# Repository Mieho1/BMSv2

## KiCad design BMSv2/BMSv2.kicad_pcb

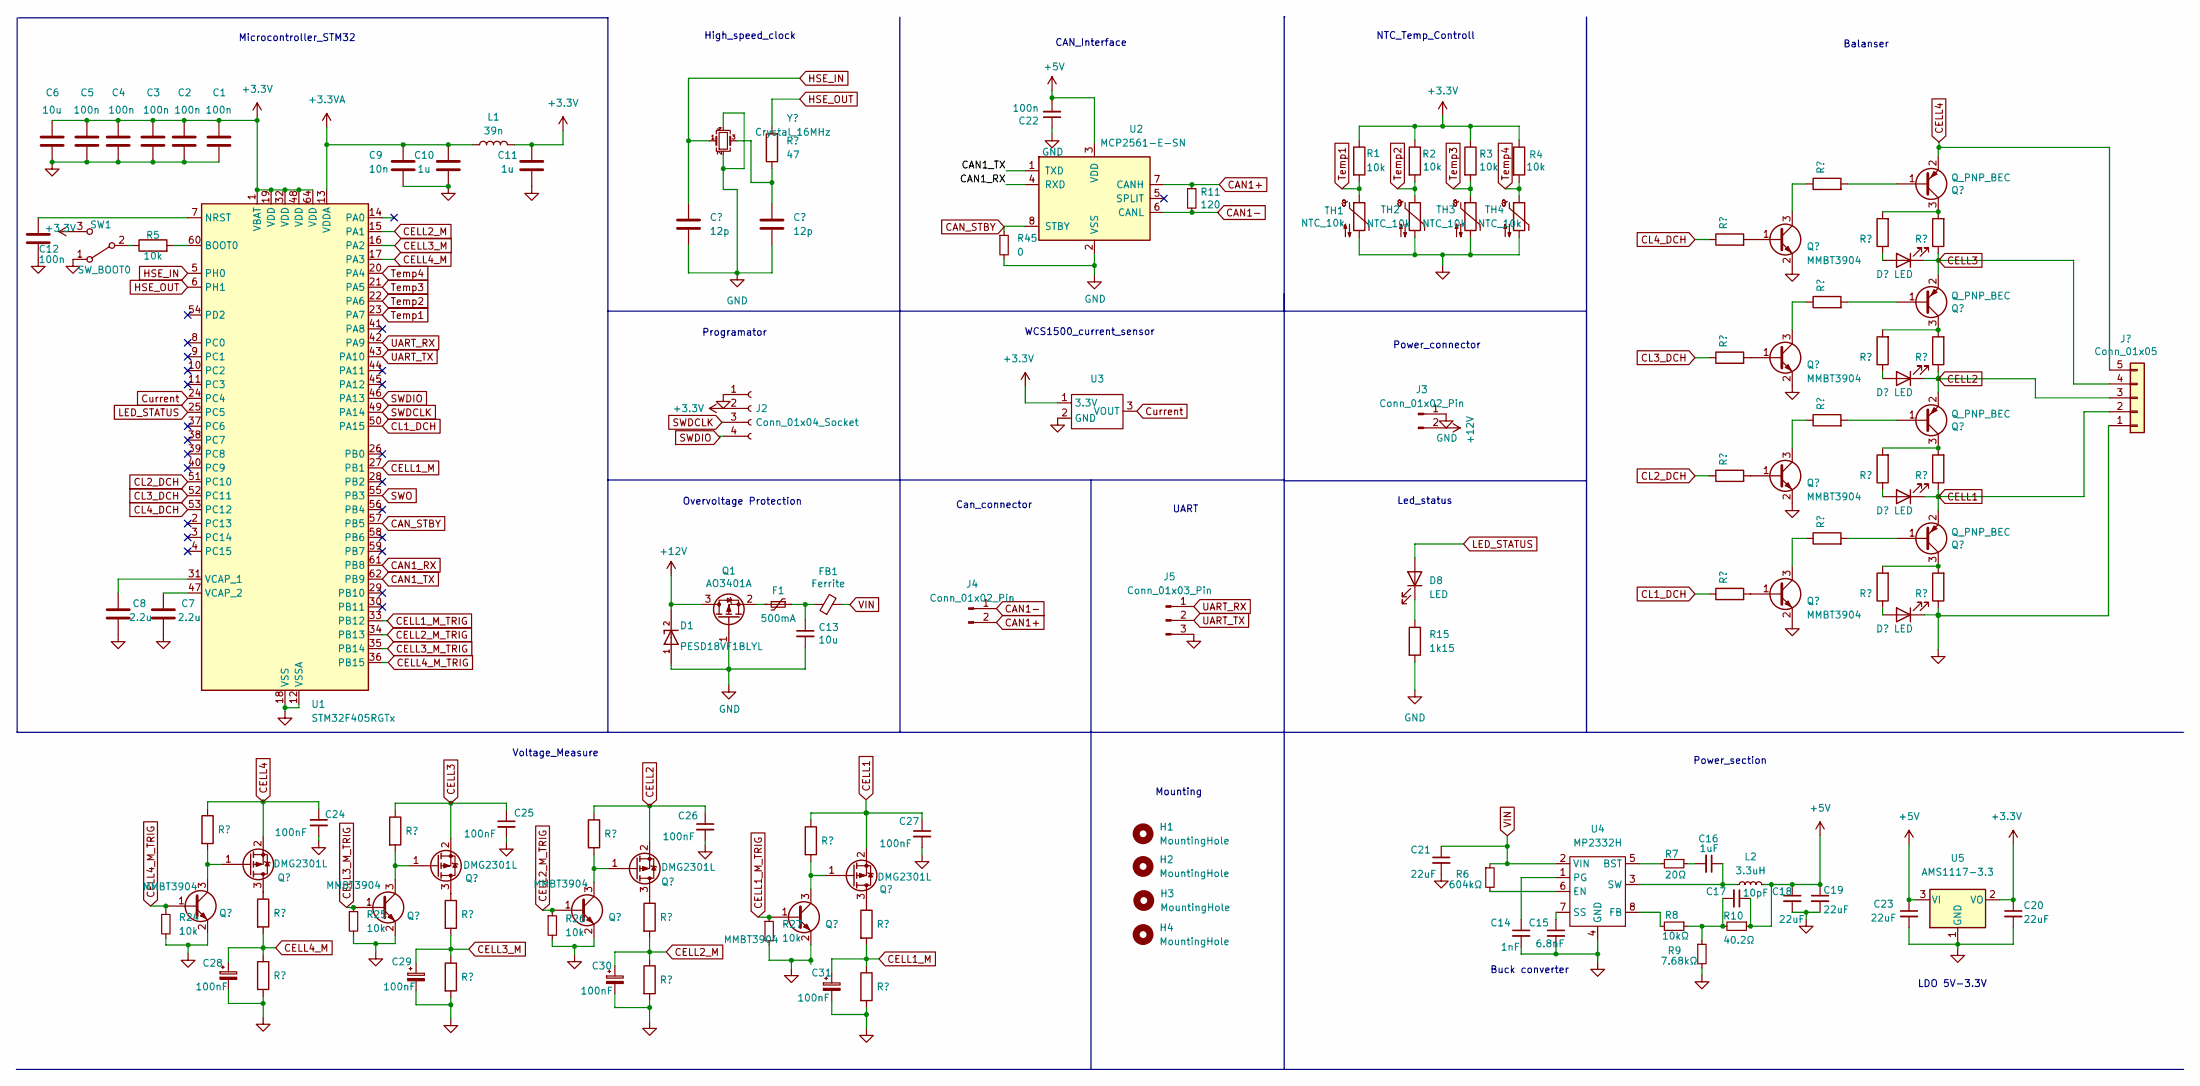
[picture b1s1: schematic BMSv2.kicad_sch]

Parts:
C1, C2, C3, C4, C5, C12, C22: 100n; C_0402_1005Metric_Pad0.74x0.62mm_HandSolder
C6, C13: 10u; C_0402_1005Metric_Pad0.74x0.62mm_HandSolder
C7, C8: 2.2u; C_0402_1005Metric_Pad0.74x0.62mm_HandSolder
C9: 10n; C_0402_1005Metric_Pad0.74x0.62mm_HandSolder
C10, C11: 1u; C_0402_1005Metric_Pad0.74x0.62mm_HandSolder
C14: 1nF; C_0402_1005Metric_Pad0.74x0.62mm_HandSolder
C15: 6.8nF; C_0402_1005Metric_Pad0.74x0.62mm_HandSolder
C16: 1uF; C_0402_1005Metric_Pad0.74x0.62mm_HandSolder
C17: 10pF; C_0402_1005Metric_Pad0.74x0.62mm_HandSolder
C18, C19, C20, C21, C23: 22uF; C_0805_2012Metric_Pad1.18x1.45mm_HandSolder
C24, C25, C26, C27, C28, C29, C30, C31: 100nF; C_0402_1005Metric_Pad0.74x0.62mm_HandSolder
C32, C33: 12p; C_0402_1005Metric
D1: PESD18VF1BLYL; PESD5V0S1BL315; PARTREV F2102
D2, D3, D4, D5: LED; LED_1206_3216Metric
D8: LED; D_0603_1608Metric
F1: 500mA; Fuse_1206_3216Metric
FB1: Ferrite; L_0805_2012Metric
H1, H2, H3, H4: MountingHole; MountingHole_2.2mm_M2
J1: Conn_01x05; JST_XH_S5B-XH-A_1x05_P2.50mm_Horizontal
J2: Conn_01x04_Socket; PinSocket_1x04_P2.54mm_Vertical
J3: Conn_01x02_Pin; Molex_PicoBlade_53048-0210_1x02_P1.25mm_Horizontal
J4: Conn_01x02_Pin; Molex_PicoBlade_53261-0271_1x02-1MP_P1.25mm_Horizontal
J5: Conn_01x03_Pin; PinHeader_1x03_P2.54mm_Vertical
L1: 39n; L_0805_2012Metric_Pad1.15x1.40mm_HandSolder
L2: 3.3uH; L_0805_2012Metric
Q1: AO3401A; SOT-23
Q2, Q4, Q6, Q8, Q10, Q11, Q12, Q13: MMBT3904; SOT-23
Q3, Q5, Q7, Q9: DMG2301L; SOT-23
Q14, Q15, Q16, Q17: Q_PNP_BEC; SOT-23
R1, R2, R3, R4, R5, R24, R25, R26, R27: 10k; R_0402_1005Metric_Pad0.72x0.64mm_HandSolder
R6: 604kΩ; R_0402_1005Metric_Pad0.72x0.64mm_HandSolder
R7: 20Ω; R_0402_1005Metric_Pad0.72x0.64mm_HandSolder
R8: 10kΩ; R_0402_1005Metric_Pad0.72x0.64mm_HandSolder
R9: 7.68kΩ; R_0402_1005Metric_Pad0.72x0.64mm_HandSolder
R10: 40.2Ω; R_0402_1005Metric_Pad0.72x0.64mm_HandSolder
R11: 120; R_0402_1005Metric_Pad0.72x0.64mm_HandSolder
R12, R14, R15, R17, R18, R20, R21, R22, R23: 1k; R_0402_1005Metric_Pad0.72x0.64mm_HandSolder
R13: 4300; R_0402_1005Metric_Pad0.72x0.64mm_HandSolder
R16: 3k; R_0402_1005Metric_Pad0.72x0.64mm_HandSolder
R19: 2k; R_0402_1005Metric_Pad0.72x0.64mm_HandSolder
R28: 47; R_0402_1005Metric
R29, R30, R31, R32: 620; R_0603_1608Metric_Pad0.98x0.95mm_HandSolder
R33: 2k; R_0603_1608Metric_Pad0.98x0.95mm_HandSolder
R34: 1.5k; R_0603_1608Metric_Pad0.98x0.95mm_HandSolder
R35: 1k; R_0603_1608Metric_Pad0.98x0.95mm_HandSolder
R36: 500; R_0603_1608Metric_Pad0.98x0.95mm_HandSolder
R37, R38, R39, R40: 120; R_0603_1608Metric_Pad0.98x0.95mm_HandSolder
R41, R42, R43, R44: 30; R_2512_6332Metric_Pad1.40x3.35mm_HandSolder
R45: 0; R_0402_1005Metric_Pad0.72x0.64mm_HandSolder
SW1: SW_BOOT0; SW_SPDT_PCM12
TH1, TH2, TH3, TH4: NTC_10k; R_LDR_5.0x4.1mm_P3mm_Vertical
U1: STM32F405RGTx; LQFP-64_10x10mm_P0.5mm
U2: MCP2561-E-SN; SOIC-8_3.9x4.9mm_P1.27mm
U3: WCS1500
U4: MP2332H; MP2332HGTL-P
U5: AMS1117-3.3; SOT-223-3_TabPin2
Y1: Crystal_16MHz; XTAL_ECS-160-10-37-JTN-TR

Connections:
+3.3V: C1.1, C2.1, C3.1, C4.1, C5.1, C6.1, C11.1, C20.1, J2.2, L1.2, R1.1, R2.1, R3.1, R4.1, SW1.3 (C), U1.1 (VBAT), U1.19 (VDD), U1.32 (VDD), U1.48 (VDD), U1.64 (VDD), U3.1 (3.3V), U5.2 (VO)
+3.3VA: C9.1, C10.1, L1.1, U1.13 (VDDA)
+5V: C17.1, C18.1, C19.1, C22.2, C23.1, L2.2, R10.1, U2.3 (VDD), U5.3 (VI)
+12V: D1.2, J3.2, Q1.3 (D)
CAN1+: J4.2, R11.1, U2.7 (CANH)
CAN1-: J4.1, R11.2, U2.6 (CANL)
CAN1_RX: U1.61 (PB8), U2.4 (RXD)
CAN1_TX: U1.62 (PB9), U2.1 (TXD)
CAN_STBY: R45.1, U1.57 (PB5), U2.8 (STBY)
CELL1: C27.1, D4.1 (K), J1.2, Q9.2 (S), Q17.2 (E), R21.1, R43.1
CELL1_M: C31.1, R22.2, R23.1, U1.27 (PB1)
CELL1_M_TRIG: Q8.1 (B), R27.1, U1.33 (PB12)
CELL2: C26.1, D3.1 (K), J1.3, Q7.2 (S), Q16.2 (E), R18.1, R42.1
CELL2_M: C30.1, R19.2, R20.1, U1.15 (PA1)
CELL2_M_TRIG: Q6.1 (B), R26.1, U1.34 (PB13)
CELL3_M: C29.1, R16.2, R17.1, U1.16 (PA2)
CELL3_M_TRIG: Q4.1 (B), R25.1, U1.35 (PB14)
CELL4: C24.1, J1.5, Q3.2 (S), Q14.2 (E), R12.1
CELL4_M: C28.1, R13.2, R14.1, U1.17 (PA3)
CELL4_M_TRIG: Q2.1 (B), R24.1, U1.36 (PB15)
CL1_DCH: R32.1, U1.50 (PA15)
CL2_DCH: R31.1, U1.51 (PC10)
CL3_DCH: R30.1, U1.52 (PC11)
CL4_DCH: R29.1, U1.53 (PC12)
Current: U1.24 (PC4), U3.3 (VOUT)
HSE_IN: C32.1, U1.5 (PH0), Y1.1
HSE_OUT: R28.2, U1.6 (PH1)
LED_STATUS: U1.25 (PC5); also elsewhere on the board
unnamed: C13.1, F1.1, FB1.1
unnamed: C16.2, R7.1
unnamed: C17.2, R8.1, R9.1, R10.2
unnamed: C33.1, R28.1, Y1.3
unnamed: D2.2 (A), R37.1
unnamed: D3.2 (A), R38.1
unnamed: D4.2 (A), R39.1
unnamed: D5.2 (A), R40.1
unnamed: F1.2, Q1.2 (S)
unnamed: Q2.3 (C), Q3.1 (G), R12.2
unnamed: Q3.3 (D), R13.1
unnamed: Q5.3 (D), R16.1
unnamed: Q6.3 (C), Q7.1 (G), R18.2
unnamed: Q7.3 (D), R19.1
unnamed: Q8.3 (C), Q9.1 (G), R21.2
unnamed: Q9.3 (D), R22.1
unnamed: Q10.1 (B), R29.2
unnamed: Q10.3 (C), R33.1
unnamed: Q11.1 (B), R30.2
unnamed: Q11.3 (C), R34.1
unnamed: Q12.1 (B), R31.2
unnamed: Q12.3 (C), R35.1
unnamed: Q13.1 (B), R32.2
unnamed: Q13.3 (C), R36.1
unnamed: Q14.1 (B), R33.2
unnamed: Q14.3 (C), R37.2, R41.2
unnamed: Q15.1 (B), R34.2
unnamed: Q15.3 (C), R38.2, R42.2
unnamed: Q16.1 (B), R35.2
unnamed: Q16.3 (C), R39.2, R43.2
unnamed: Q17.1 (B), R36.2
unnamed: Q17.3 (C), R40.2, R44.2
unnamed: R5.1, SW1.2 (B)
unnamed: R5.2, U1.60 (BOOT0)
unnamed: C12.1, U1.7 (NRST)
unnamed: C8.1, U1.31 (VCAP_1)
unnamed: C7.1, U1.47 (VCAP_2)
unnamed: R7.2, U4.5 (BST)
unnamed: R6.2, U4.6 (EN)
unnamed: R8.2, U4.8 (FB)
unnamed: C14.1, U4.1 (PG)
unnamed: C15.1, U4.7 (SS)
unnamed: C16.1, L2.1, U4.3 (SW)
SWDCLK: J2.3, U1.49 (PA14)
SWDIO: J2.4, U1.46 (PA13)
SWO: U1.55 (PB3)
Temp1: R1.2, TH1.1, U1.23 (PA7)
Temp2: R2.2, TH2.1, U1.22 (PA6)
Temp3: R3.2, TH3.1, U1.21 (PA5)
Temp4: R4.2, TH4.1, U1.20 (PA4)
UART_RX: J5.1, U1.42 (PA9)
UART_TX: J5.2, U1.43 (PA10)
VIN: C21.1, FB1.2, R6.1, U4.2 (VIN)

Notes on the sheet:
High_speed_clock
Can_connector
Microcontroller_STM32
Voltage_Measure
Led_status
Overvoltage Protection
Power_section
CAN_Interface
Programator
Power_connector
UART
WCS1500_current_sensor
Mounting
Balanser
NTC_Temp_Controll
LDO 5V-3.3V
Buck converter

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
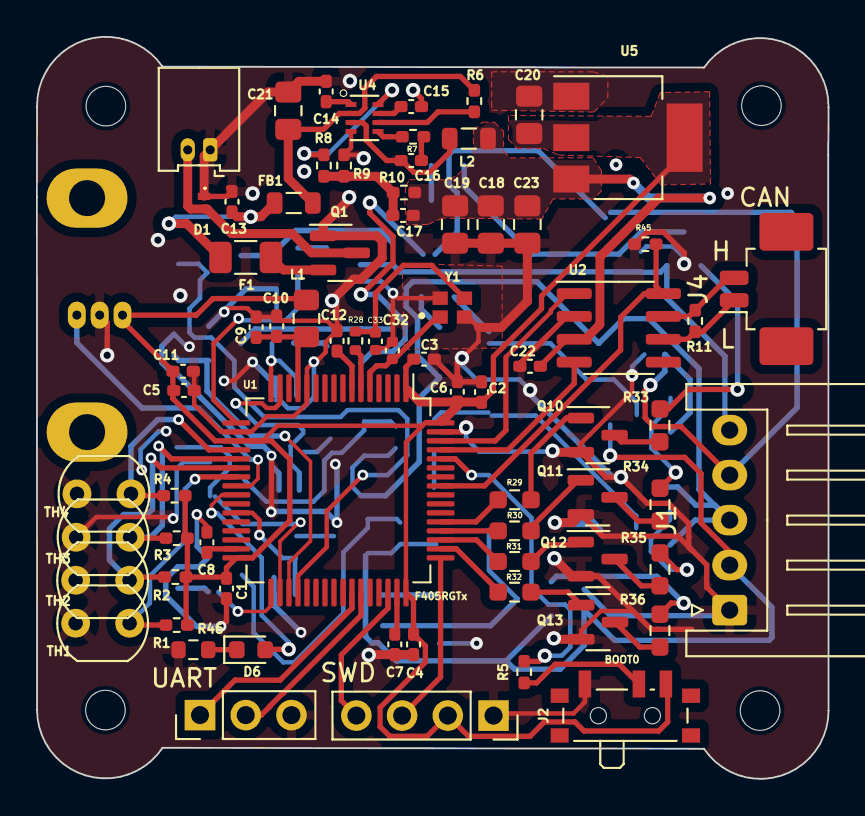
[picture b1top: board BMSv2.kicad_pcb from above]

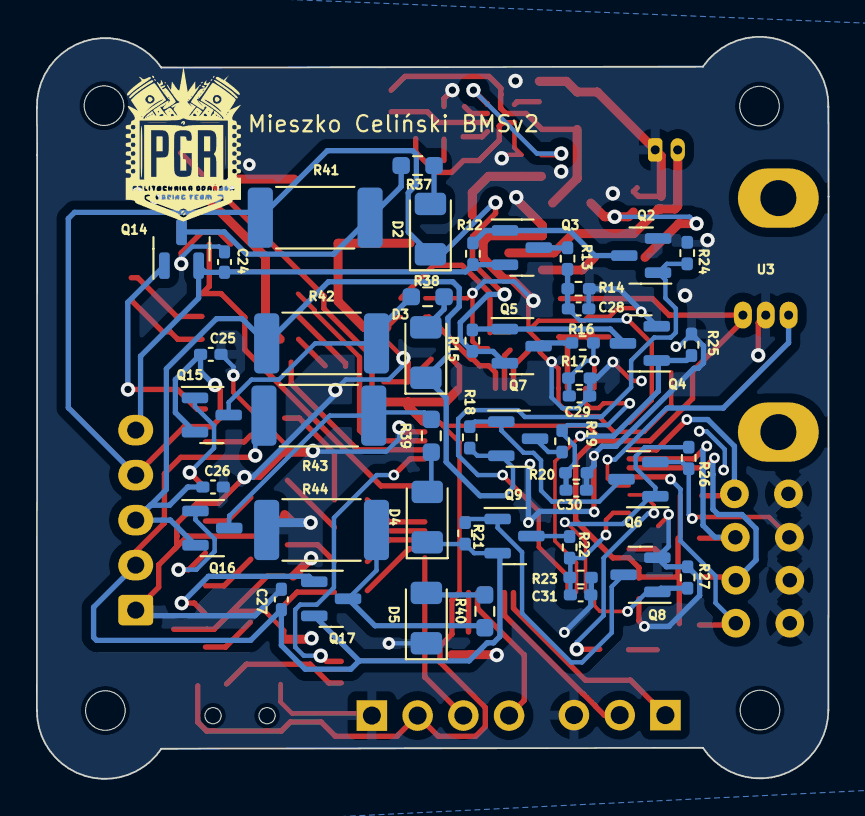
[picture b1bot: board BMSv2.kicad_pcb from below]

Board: 2 copper layers, 44.0 x 41.2 mm, 126 parts (49 on the bottom side), 84 nets.

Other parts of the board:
D6: LED; D_0603_1608Metric
R46: 1k15; R_0603_1608Metric

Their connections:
LED_STATUS: D6.2 (A); also elsewhere on the board

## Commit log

2023-10-16 Rooting for power section
2023-10-18 Added for Front flayer
2023-10-19 fast commit
2023-10-19 Solving DRC Errors
2023-10-21 GND connected
2023-10-25 DRC Errors deletion
2023-10-25 added BOM and changed Vias
2023-10-26 silkscreen improvment
2023-10-31 added PGR slikscreen and export gerber files
